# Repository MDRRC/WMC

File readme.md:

Wifi Manual Control
=====================

The Wifi Manual Control (Wmc) is a project which supports the [Z21 protocol](https://www.z21.eu/en) of [Roco](https://www.roco.cc/en/home/index.html) to control locomotives and turnouts. Also CV's can be read and written. 
The design is based on an ESP8266-12E processor (Wemos Mini D1 for example), an ST7735 1.44 inch display, rotary (pulse) switch and some push buttons. 
For more info see the [wiki](https://github.com/MDRRC/WMC/wiki).

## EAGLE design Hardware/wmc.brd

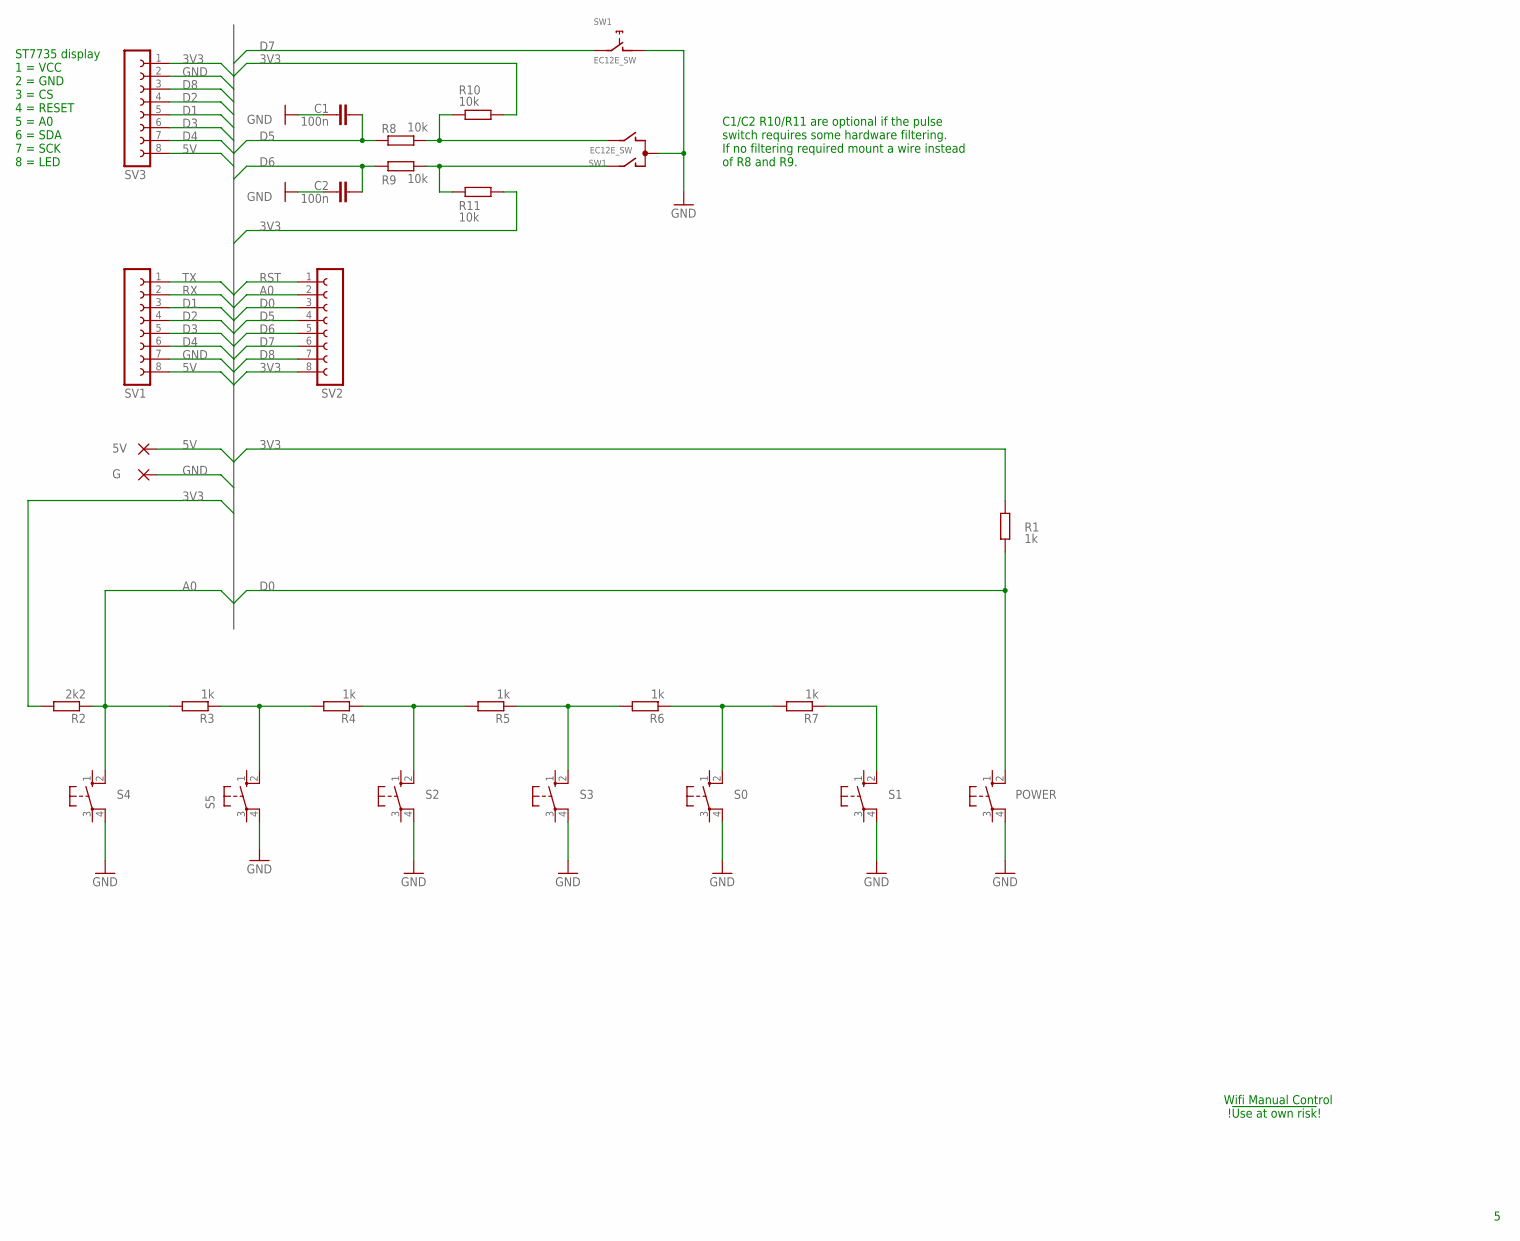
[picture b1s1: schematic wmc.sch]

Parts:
5V: 1,6/0,8
C1, C2: 100n; C025-024X044
G: 1,6/0,8
POWER: 10-XX; B3F-10XX
R1, R3, R4, R5, R6, R7: 1k; 0309/10
R2: 2k2; 0309/10
R8, R9, R10, R11: 10k; 0207/10
S0, S1, S2, S3, S4, S5: 10-XX; B3F-10XX
SV1, SV2, SV3: FE08-1; FE08
SW1: EC12E_SW; ALPS_EC12E_SW

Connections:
3V3: R1.2, R2.2, R10.2, R11.2, SV2.8, SV3.1
5V: 5V.1, SV1.8, SV3.8
A0: R2.1, R3.2, S4.2 (S1), SV2.2
D0: POWER.2 (S1), R1.1, SV2.3
D1: SV1.3, SV3.5
D2: SV1.4, SV3.4
D3: SV1.5, SV3.6
D4: SV1.6, SV3.7
D5: C1.1, R8.1, SV2.4
D6: C2.1, R9.1, SV2.5
D7: SV2.6, SW1.E (2)
D8: SV2.7, SV3.3
GND: C1.2, C2.2, G.1, POWER.4 (P1), S0.4 (P1), S1.4 (P1), S2.4 (P1), S3.4 (P1), S4.4 (P1), S5.4 (P1), SV1.7, SV3.2, SW1.C, SW1.D (1)
unnamed: R7.1, S1.2 (S1)
unnamed: R3.1, R4.2, S5.2 (S1)
unnamed: R4.1, R5.2, S2.2 (S1)
unnamed: R5.1, R6.2, S3.2 (S1)
unnamed: R6.1, R7.2, S0.2 (S1)
unnamed: R8.2, R10.1, SW1.B
unnamed: R9.2, R11.1, SW1.A
RST: SV2.1
RX: SV1.2
TX: SV1.1

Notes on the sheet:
Wifi Manual Control !!Use at own risk!!
ST7735 display 1 = VCC 2 = GND 3 = CS 4 = RESET 5 = A0 6 = SDA 7 = SCK 8 = LED
C1/C2 R10/R11 are optional if the pulse switch requires some hardware filtering. If no filtering required mount a wire instead of R8 and R9.

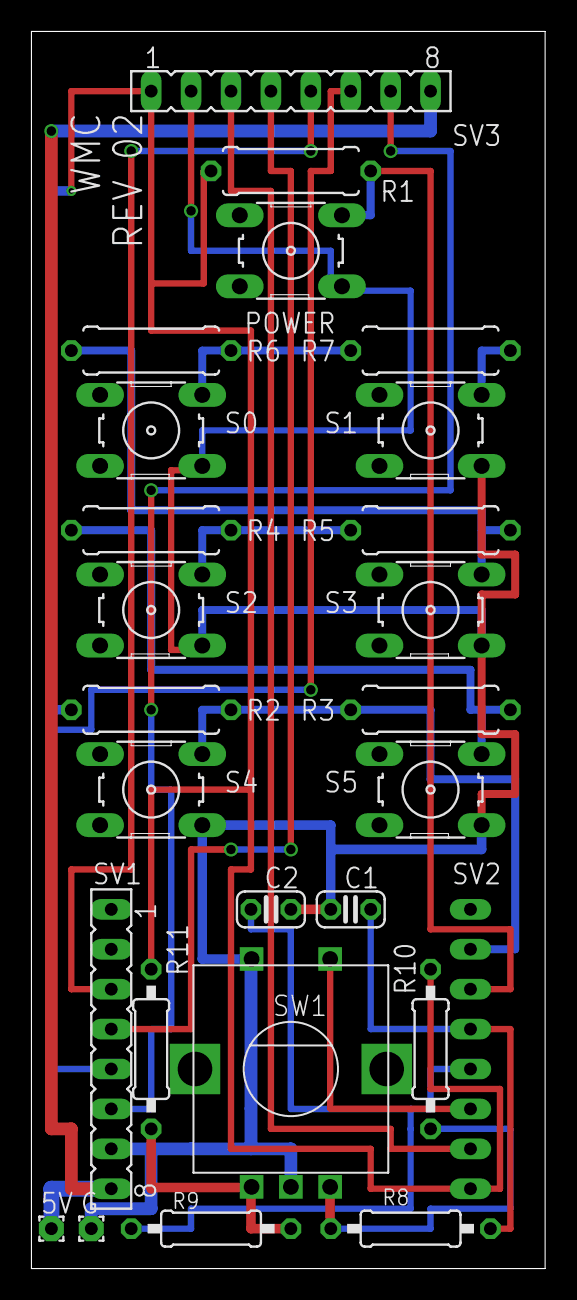
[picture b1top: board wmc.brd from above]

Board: 2 copper layers, 32.7 x 78.7 mm, 26 parts (1 on the bottom side), 20 nets.

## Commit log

2017-10-08 Wmc : Added.
2017-10-09 Put files in own dir.
2017-10-09 Deleted, is now in image dir.
2017-10-09 Added picture.
2017-10-11 Added file.
2017-10-11 Typo's corrected.
2017-10-11 Typo.
2017-10-11 Picture updated.
2017-10-15 Added.
2017-10-16 Extra check states and received data to avoid overwriting status row each time.
2017-10-16 Schematic corrected.
2017-10-22 Command line interface added. State handling (checks) updated.
2017-11-27 Cleanup of code, control of application is moved to WmcApp. This file now only performs triggering of events to the central state machine.
2017-11-27 Updated text.
2017-11-27 Added comment and timed events handling updated.
2017-12-18 Uodated image with extra switch and updated resistors.
2017-12-18 Analog values for switches updated after adding 5th switch.
2018-02-04 Timer test of WmcUpdatePulseSwitch wrong, corrected it.
2018-03-21 Rotary (pulse) switch inputs use internal pull ups of the ESP8266.
2018-03-25 Use event header file.
2018-05-01 Added schematic.
2018-05-01 Updated image.
2018-05-05 Added document for mounting components onm PCB and programming the ESP8266 module without the need for a full developer version on a PC.
2018-05-05 Added bin file for PCB version 01.
2018-05-17 Document updated. * 1 Introduction. Added link to how to operate the WMC. * 3 Programming. Filename and screenshot updated.
2018-06-09 Added dutch manual created by Paul http://members.home.nl/pamali/
2018-06-09 Numbering of the buttons changed so on the PCB S0 is left upper, S1 is right upper and so on. A more logical assignment of the buttons.
2018-06-28 Cleanup of file, events updated and command line interface removed.
2018-06-28 Bin file updated to most recent status.
2018-07-09 Hard coded time replaced with define and removed non used define.
2018-07-09 Added RC combination for filtering pulse switch.
2018-08-02 Missing labels added for pulse switch bus signals.
2018-08-06 Replaced bin file with version info at startup.
2018-08-27 Bin file updated, version 1.00.01
2018-08-27 Bin file version 1.00.01 after menu text update.
2018-08-29 Bin file of version 1.1.0.
2018-08-29 Added (Dutch language) OpenOffice Calc sheet with overview of menu's and actions. Sheet is created by Paul ( http://members.home.nl/pamali/ ).
2018-09-02 Bin file with emergency stop option.
2018-09-23 Added enlarged component PCB overview of the REV01 version. This version has NO extra components for the pulse switch and has the missing 3V3 supply voltage to the LCD.
2018-11-16 R2 changes to 2K2 for better adc levels of pressed switches.
2018-11-17 Updated for REV02 version. Please use 2k2 for R2 instead of 1K for better detection of buttons connected to the ADC input.
2018-11-17 Non use define removed.
2018-11-18 Version 2.0.1, this version clears EEPROM when updating from older version to 2.0.1. Updating from Version 2.0.0 will not lead to clear of EEPROM.
2018-11-18 Bin file updated after adding emergency option in command line.
2019-01-09 Pulse switch handling updated.
2019-01-09 Bin file updated.
2019-01-09 Updated bin file with display of IP address where WMC tries to connect to.
2019-01-30 Updated.
2019-06-12 Replaced bin file.
2019-06-23 Replaced bin file, 03_00_00 has supprt for adding the name to a loc and some updates in text and command line interface handling.
    Ne aware, most of the settings might be lost. Best is to do a araseall after programming.
2019-06-23 Updated picture.
2019-06-28 Replaced bin file, 3.00.01 processes locomotive names received over Z21 loc data base commands.
2019-07-02 Version 3.00.02 to transmit locomotive data to a Z21 master (only tested with MDRRC-II(Lite)!!)
2019-07-02 Power off command when entering menu removed.
2019-10-30 Version 3.00.03.
2020-01-28 Added 5msec event handling for faster processing of network responses.
2020-03-14 Indent of code.
2020-04-27 * The interrupt is changed to CHANGE. For best performence add "debounce" resistors and capacitors. * Replaced bin file.
2020-04-27 Added bin file.
2020-09-21 Added screenshot setting Sloeber.
2020-09-21 Added screenshot settings Sloeber for WMC project.
2020-09-21 Text updated.
2020-09-21 Replaced bin file. This bin file has the 64 bytes Wifi password option. If it works now at you WMC do not update, you will loos settings and need to set the Wifi settings for example.
2020-10-12 Added image.
2020-10-19 Updated interrupt declaration of encoder input.
2020-10-19 Version 3.1.1
    * Direction change corrected.
    * When deleting show delete during deleting.
    * Changing functions updates so new functions are displayed when going back to normal control.
2020-11-03 1.1 Used components Test of resistors updated.
2020-11-08 Bin file version 3.02.00. * Added option to change pulse switch direction using command pulse.
2020-12-02 Version 3.02.01, function display corrected.
2020-12-18 Added handling for released event (loc selection).
2020-12-26 Added Eagle files.
2020-12-29 Version 3.03.03 * Loc selection made faster. During selecting a loc no data is requested from the command station about the loc, only when the push button is released. * Turnout off command corrected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
2022-01-12 Added version 3.03.01. When in cv mode and pressing short no exit from cv anymore, was quite irritating. Exit cv mode is now power button.
2022-11-17 Replaced bin file with latest version 3.03.02.
